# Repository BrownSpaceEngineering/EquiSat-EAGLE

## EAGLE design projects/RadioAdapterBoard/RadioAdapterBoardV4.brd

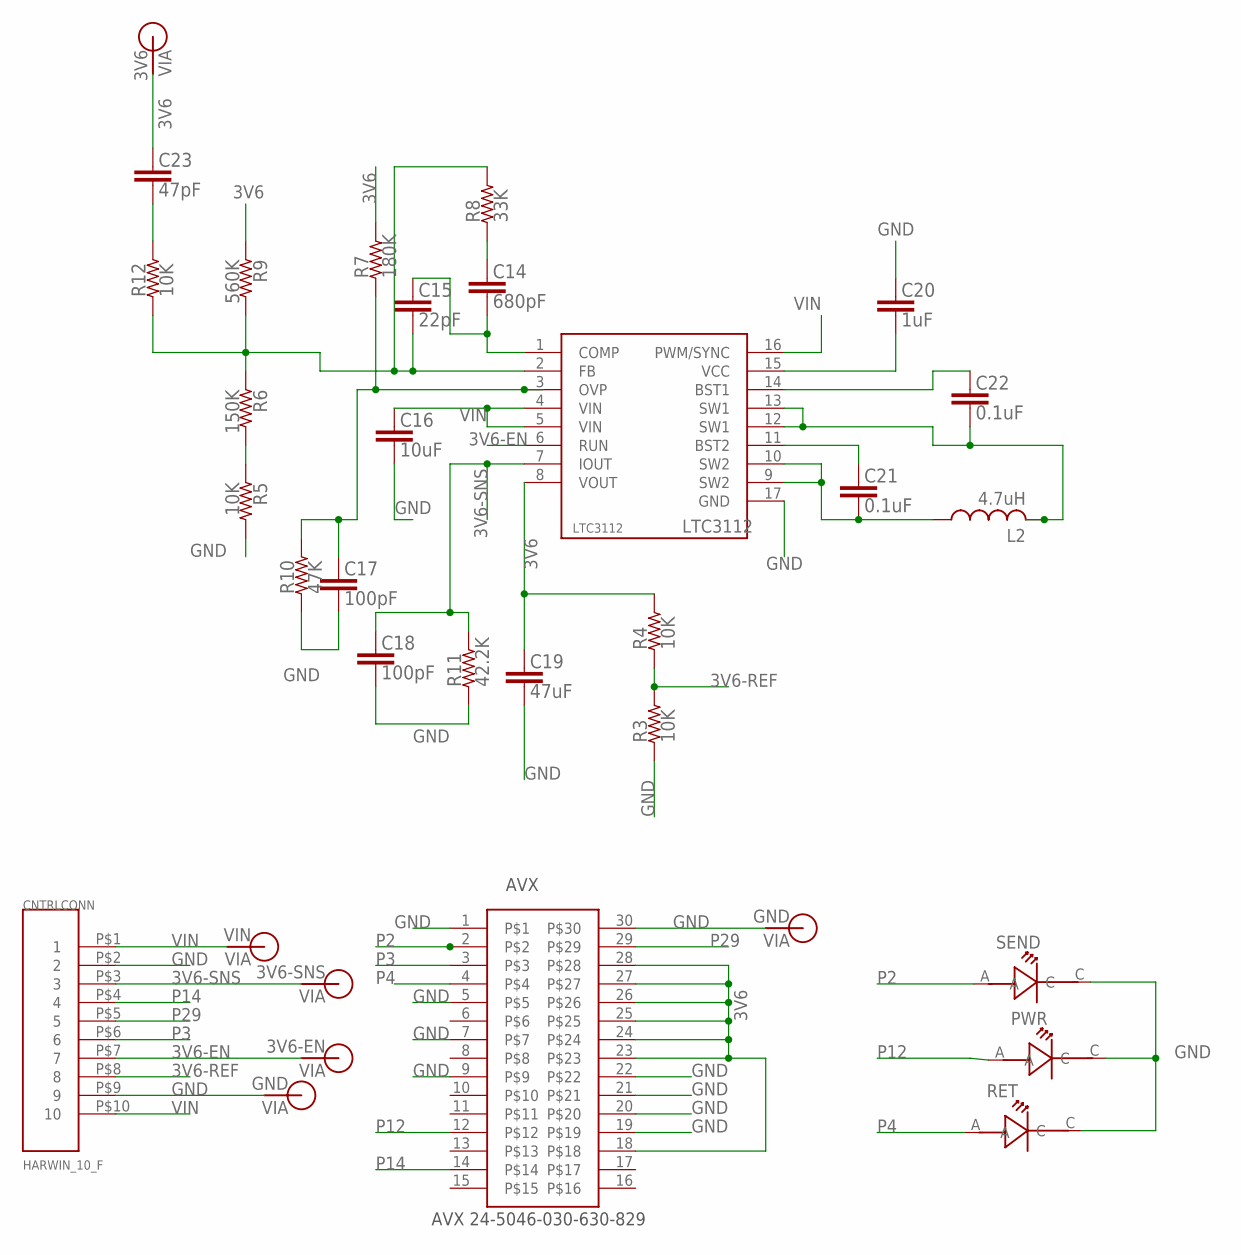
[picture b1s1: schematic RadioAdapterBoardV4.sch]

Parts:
AVX: AVX-24-5046-030-630-829; AVX-24-5046-630-829
C14: 680pF; 0805
C15: 22pF; 0805
C16: 10uF; 0805
C17, C18: 100pF; 0805
C19: 47uF; 0805
C20: 1uF; 0805
C21, C22: 0.1uF; 0805
C23: 47pF; 0805
CNTRLCONN: HARWIN_10_F; HARWIN_DATAMATE_10_F
L2: 4.7uH; L3225M
LTC3112: LTC3112; DHD16
PWR: LT-T673-Q1R2-25-Z; PLCC-2
R3, R4, R5, R12: 10K; 0805
R6: 150K; 0805
R7: 180K; 0805
R8: 33K; 0805
R9: 560K; 0805
R10: 47K; 0805
R11: 42.2K; 0805
RET: LT-T673-Q1R2-25-Z; PLCC-2
SEND: LT-T673-Q1R2-25-Z; PLCC-2
V1: VIN; VIA-60MIL-SQ
V2: 3V6-SNS; VIA-60MIL-SQ
V3, V4: GND; VIA-60MIL-SQ
V5: 3V6; VIA-60MIL-SQ
V6: 3V6-EN; VIA-60MIL-SQ

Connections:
3V6: AVX.18, AVX.23, AVX.24, AVX.25, AVX.26, AVX.27, AVX.28, C19.1, C23.1, LTC3112.8 (VOUT), R4.2, R7.2, R9.1, V5.P$1
3V6-EN: CNTRLCONN.P$7 (7), LTC3112.6 (RUN), V6.P$1
3V6-REF: CNTRLCONN.P$8 (8), R3.2, R4.1
3V6-SNS: C18.1, CNTRLCONN.P$3 (3), LTC3112.7 (IOUT), R11.2, V2.P$1
COMP: C14.2, C15.1, LTC3112.1 (COMP)
FB: C15.2, LTC3112.2 (FB), R6.1, R8.2, R9.2, R12.1
GND: AVX.1, AVX.5, AVX.7, AVX.9, AVX.19, AVX.20, AVX.21, AVX.22, AVX.30, C16.2, C17.2, C18.2, C19.2, C20.1, CNTRLCONN.P$2 (2), CNTRLCONN.P$9 (9), LTC3112.17 (GND), PWR.C, R3.1, R5.2, R10.1, R11.1, RET.C, SEND.C, V3.P$1, V4.P$1
unnamed: C14.1, R8.1
unnamed: C23.2, R12.2
unnamed: R5.1, R6.2
unnamed: C20.2, LTC3112.15 (VCC)
unnamed: C22.1, LTC3112.14 (BST1)
unnamed: C22.2, L2.2, LTC3112.12 (SW1), LTC3112.13 (SW1)
unnamed: C21.2, L2.1, LTC3112.9 (SW2), LTC3112.10 (SW2)
unnamed: C21.1, LTC3112.11 (BST2)
OVP: C17.1, LTC3112.3 (OVP), R7.1, R10.2
P2: AVX.2, SEND.A
P3: AVX.3, CNTRLCONN.P$6 (6)
P4: AVX.4, RET.A
P12: AVX.12, PWR.A
P14: AVX.14, CNTRLCONN.P$4 (4)
P29: AVX.29, CNTRLCONN.P$5 (5)
VIN: C16.1, CNTRLCONN.P$1 (1), CNTRLCONN.P$10 (10), LTC3112.4 (VIN), LTC3112.5 (VIN), LTC3112.16 (PWM/SYNC), V1.P$1

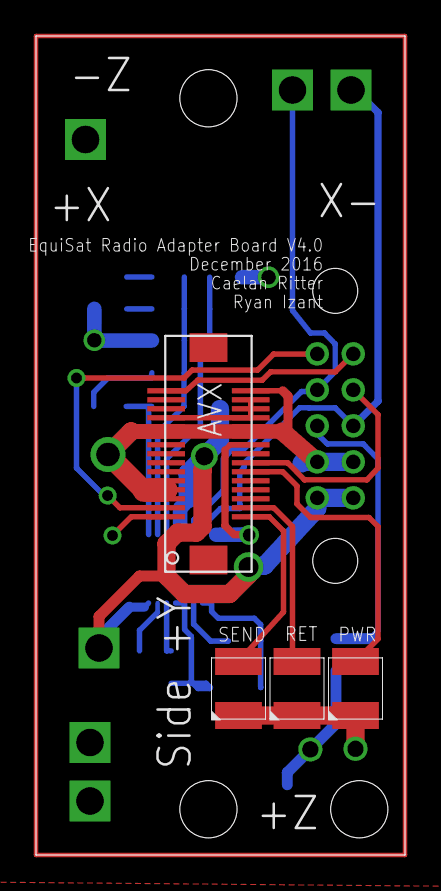
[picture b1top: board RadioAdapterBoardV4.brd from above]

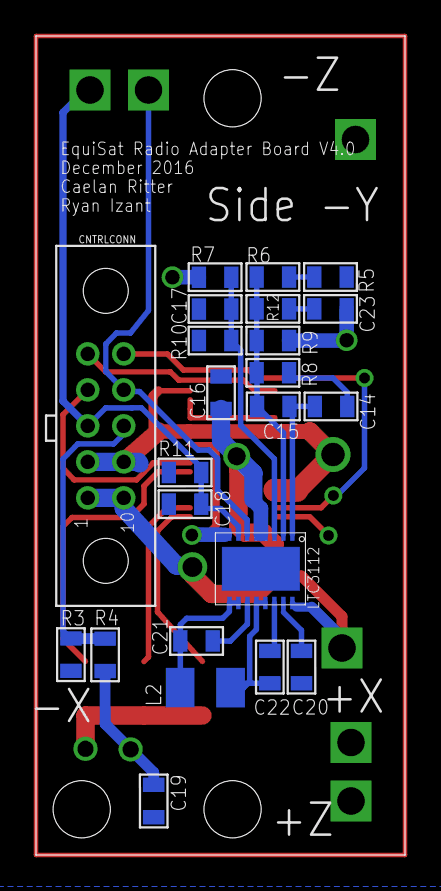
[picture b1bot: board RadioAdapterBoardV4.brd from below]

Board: 2 copper layers, 20.5 x 45.5 mm, 33 parts (23 on the bottom side), 23 nets.

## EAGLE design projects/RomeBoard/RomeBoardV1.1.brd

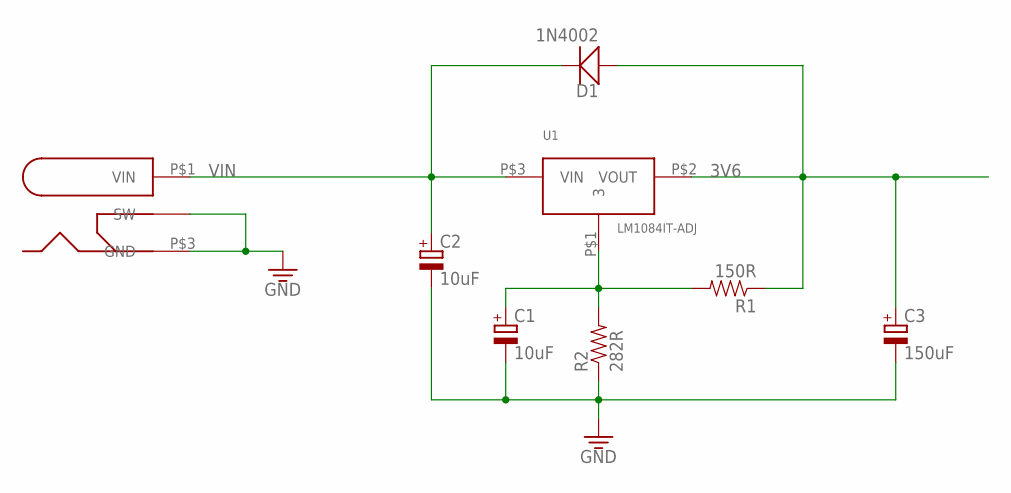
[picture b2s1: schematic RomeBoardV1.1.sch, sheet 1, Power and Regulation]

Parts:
C1, C2: 10uF; E2,5-7
C3: 150uF; E5-13
D1: 1N4002; DO-201AD
R1: 150R; AXIAL-0.4
R2: 282R; AXIAL-0.4
U1: LM1084IT-ADJ; TO-220-507302B00000G
U$2: PJ-002A

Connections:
3V6: C3.+, D1.P$1 (A), R1.1, U1.P$2 (VOUT); also elsewhere on the board
GND: C1.-, C2.-, C3.-, R2.1, U$2.P$2 (SW), U$2.P$3 (GND); also elsewhere on the board
unnamed: C1.+, R1.2, R2.2, U1.P$1 (3)
VIN: C2.+, D1.P$2 (C), U1.P$3 (VIN), U$2.P$1 (VIN); also elsewhere on the board

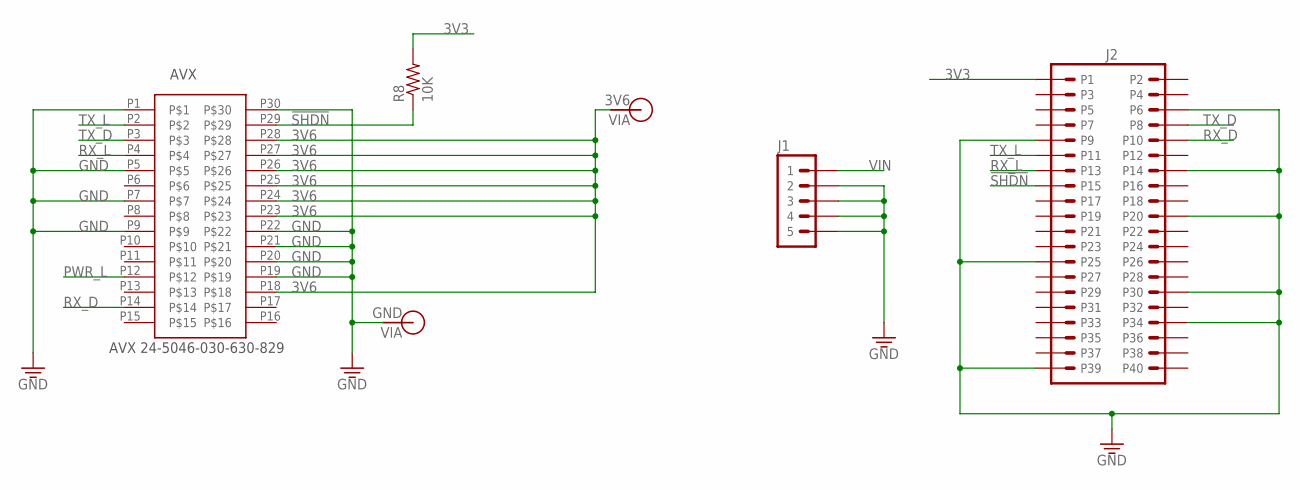
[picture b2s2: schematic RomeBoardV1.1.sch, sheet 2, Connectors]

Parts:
AVX: AVX-24-5046-030-630-829; AVX-24-5046-630-829
J1: HEADER-5; HEADER-05
J2: RASPBERRY-PI-HEADER; HEADER-20X02
R8: 10K; AXIAL-0.4
V4: GND; VIA-120MIL
V5: 3V6; VIA-120MIL

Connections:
3V3: J2.P1, R8.2
3V6: AVX.P18, AVX.P23, AVX.P24, AVX.P25, AVX.P26, AVX.P27, AVX.P28, V5.P$1; also elsewhere on the board
!SHDN: AVX.P29, J2.P15, R8.1
GND: AVX.P1, AVX.P5, AVX.P7, AVX.P9, AVX.P19, AVX.P20, AVX.P21, AVX.P22, AVX.P30, J1.2, J1.3, J1.4, J1.5, J2.P6, J2.P9, J2.P14, J2.P20, J2.P25, J2.P30, J2.P34, J2.P39, V4.P$1; also elsewhere on the board
PWR_L: AVX.P12; also elsewhere on the board
RX_D: AVX.P14, J2.P10; also elsewhere on the board
RX_L: AVX.P4, J2.P13; also elsewhere on the board
TX_D: AVX.P3, J2.P8; also elsewhere on the board
TX_L: AVX.P2, J2.P11; also elsewhere on the board
VIN: J1.1; also elsewhere on the board

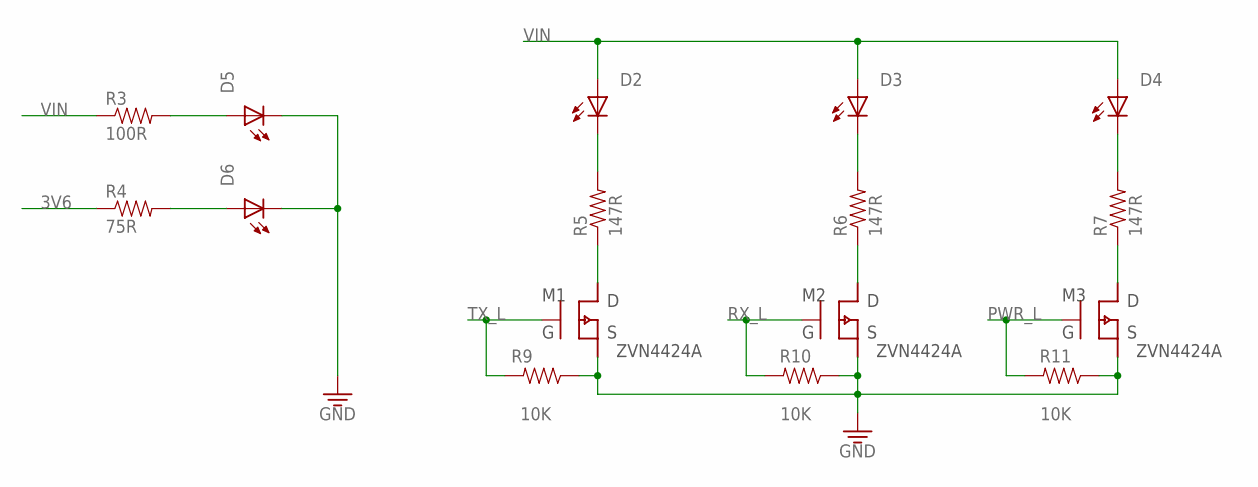
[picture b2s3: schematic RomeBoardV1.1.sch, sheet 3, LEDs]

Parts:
D2, D3, D4, D5, D6: LEDTHRU-HOLE-CONNECTOR; 1X2-POL
M1, M2, M3: ZVN4424A; TO-923-MOS
R3: 100R; AXIAL-0.4
R4: 75R; AXIAL-0.4
R5, R6, R7: 147R; AXIAL-0.4
R9, R10, R11: 10K; AXIAL-0.4

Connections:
3V6: R4.1; also elsewhere on the board
GND: D5.2 (C), D6.2 (C), M1.3 (S), M2.3 (S), M3.3 (S), R9.1, R10.1, R11.1; also elsewhere on the board
unnamed: D5.1 (A), R3.2
unnamed: D6.1 (A), R4.2
unnamed: D3.2 (C), R6.2
unnamed: M1.1 (D), R5.1
unnamed: M2.1 (D), R6.1
unnamed: M3.1 (D), R7.1
unnamed: D4.2 (C), R7.2
unnamed: D2.2 (C), R5.2
PWR_L: M3.2 (G), R11.2; also elsewhere on the board
RX_L: M2.2 (G), R10.2; also elsewhere on the board
TX_L: M1.2 (G), R9.2; also elsewhere on the board
VIN: D2.1 (A), D3.1 (A), D4.1 (A), R3.1; also elsewhere on the board

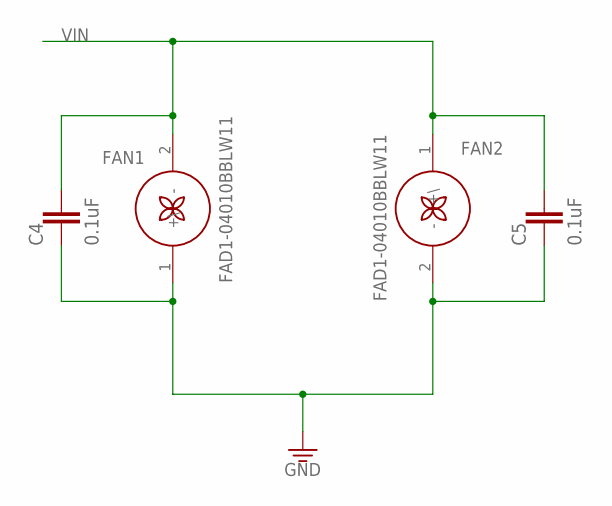
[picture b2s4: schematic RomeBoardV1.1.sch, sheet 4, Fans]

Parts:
C4, C5: 0.1uF; C050-025X075
FAN1, FAN2: FAD1-04010BBLW11; 1X2-POL

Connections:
GND: C4.2, C5.2, FAN1.1 (+\), FAN2.2 (-); also elsewhere on the board
VIN: C4.1, C5.1, FAN1.2 (-), FAN2.1 (+\); also elsewhere on the board

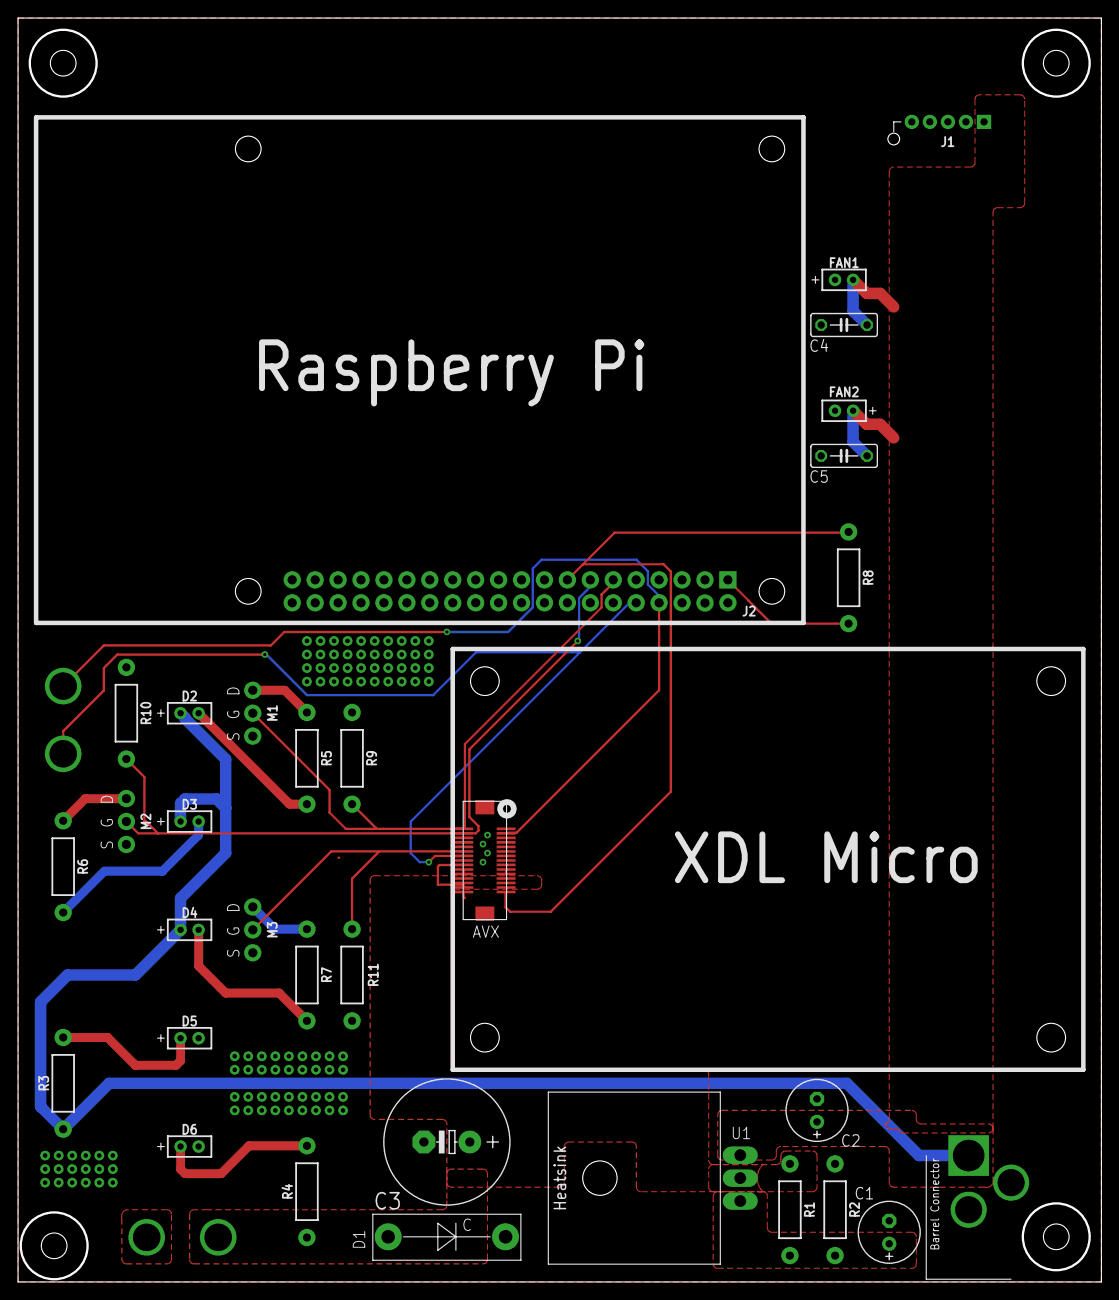
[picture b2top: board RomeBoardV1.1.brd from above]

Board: 2 copper layers, 120.0 x 140.0 mm, 36 parts (0 on the bottom side), 19 nets.

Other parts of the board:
V1: TX_D; VIA-120MIL
V2: RX_D; VIA-120MIL

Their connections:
RX_D: V2.P$1; also elsewhere on the board
TX_D: V1.P$1; also elsewhere on the board

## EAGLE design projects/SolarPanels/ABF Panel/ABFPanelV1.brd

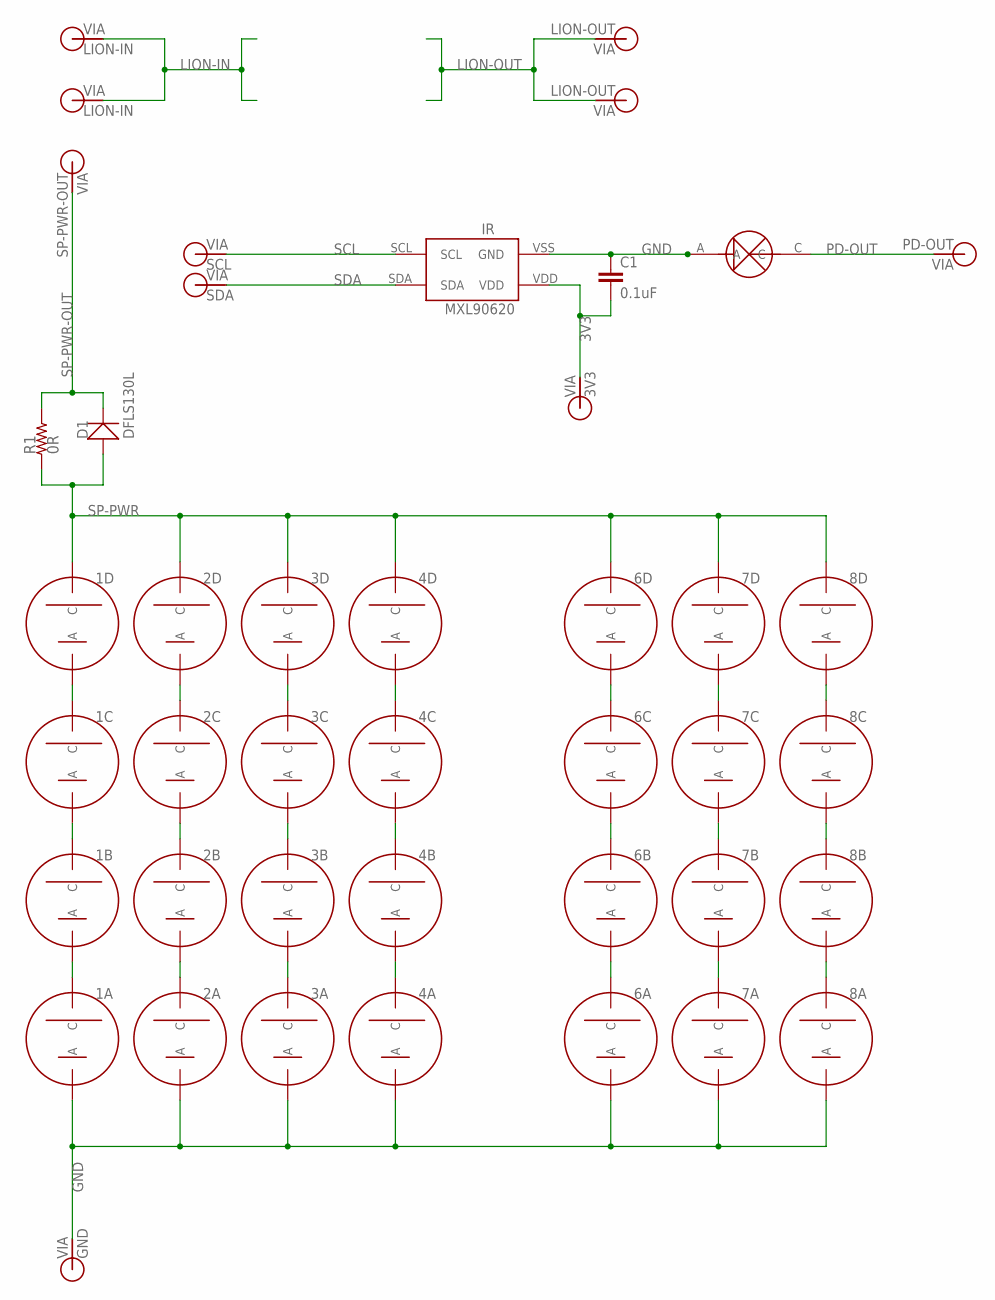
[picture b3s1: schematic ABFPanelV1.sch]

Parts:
1A, 1B, 1C, 1D, 2A, 2B, 2C, 2D, 3A, 3B, 3C, 3D, 4A, 4B, 4C, 4D, 6A, 6B, 6C, 6D, 7A, 7B, 7C, 7D, 8A, 8B, 8C, 8D: SOLARCELLV3; TRISOLX-V3
3V3: 3V3; VIA-60MIL
C1: 0.1uF; 0805
D1: DFLS130L; PWRDI-123
GND: GND; VIA-60MIL
IR: MXL90620
PD: PHOTODETECTOR; PHOTODECTORDEVICE2
PD-OUT: PD-OUT; VIA-60MIL
PWR-OUT: SP-PWR-OUT; VIA-60MIL
R1: 0R; 1210
SCL: SCL; VIA-60MIL
SDA: SDA; VIA-60MIL
V1, V2: LION-IN; VIA-60MIL
V3, V4: LION-OUT; VIA-60MIL

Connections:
3V3: 3V3.P$1, C1.2, IR.VDD
GND: 1A.ANODE (A), 2A.ANODE (A), 3A.ANODE (A), 4A.ANODE (A), 6A.ANODE (A), 7A.ANODE (A), 8A.ANODE (A), C1.1, GND.P$1, IR.VSS (GND), PD.A
LION-IN: V1.P$1, V2.P$1
LION-OUT: V3.P$1, V4.P$1
unnamed: 2C.CATHODE (C), 2D.ANODE (A)
unnamed: 1C.CATHODE (C), 1D.ANODE (A)
unnamed: 1B.CATHODE (C), 1C.ANODE (A)
unnamed: 1A.CATHODE (C), 1B.ANODE (A)
unnamed: 2B.CATHODE (C), 2C.ANODE (A)
unnamed: 2A.CATHODE (C), 2B.ANODE (A)
unnamed: 3C.CATHODE (C), 3D.ANODE (A)
unnamed: 3B.CATHODE (C), 3C.ANODE (A)
unnamed: 3A.CATHODE (C), 3B.ANODE (A)
unnamed: 4C.CATHODE (C), 4D.ANODE (A)
unnamed: 4B.CATHODE (C), 4C.ANODE (A)
unnamed: 4A.CATHODE (C), 4B.ANODE (A)
unnamed: 6C.CATHODE (C), 6D.ANODE (A)
unnamed: 6B.CATHODE (C), 6C.ANODE (A)
unnamed: 6A.CATHODE (C), 6B.ANODE (A)
unnamed: 7C.CATHODE (C), 7D.ANODE (A)
unnamed: 7B.CATHODE (C), 7C.ANODE (A)
unnamed: 7A.CATHODE (C), 7B.ANODE (A)
unnamed: 8C.CATHODE (C), 8D.ANODE (A)
unnamed: 8B.CATHODE (C), 8C.ANODE (A)
unnamed: 8A.CATHODE (C), 8B.ANODE (A)
PD-OUT: PD.C, PD-OUT.P$1
SCL: IR.SCL, SCL.P$1
SDA: IR.SDA, SDA.P$1
SP-PWR: 1D.CATHODE (C), 2D.CATHODE (C), 3D.CATHODE (C), 4D.CATHODE (C), 6D.CATHODE (C), 7D.CATHODE (C), 8D.CATHODE (C), D1.A, R1.P$1 (1)
SP-PWR-OUT: D1.C, PWR-OUT.P$1, R1.P$2 (2)

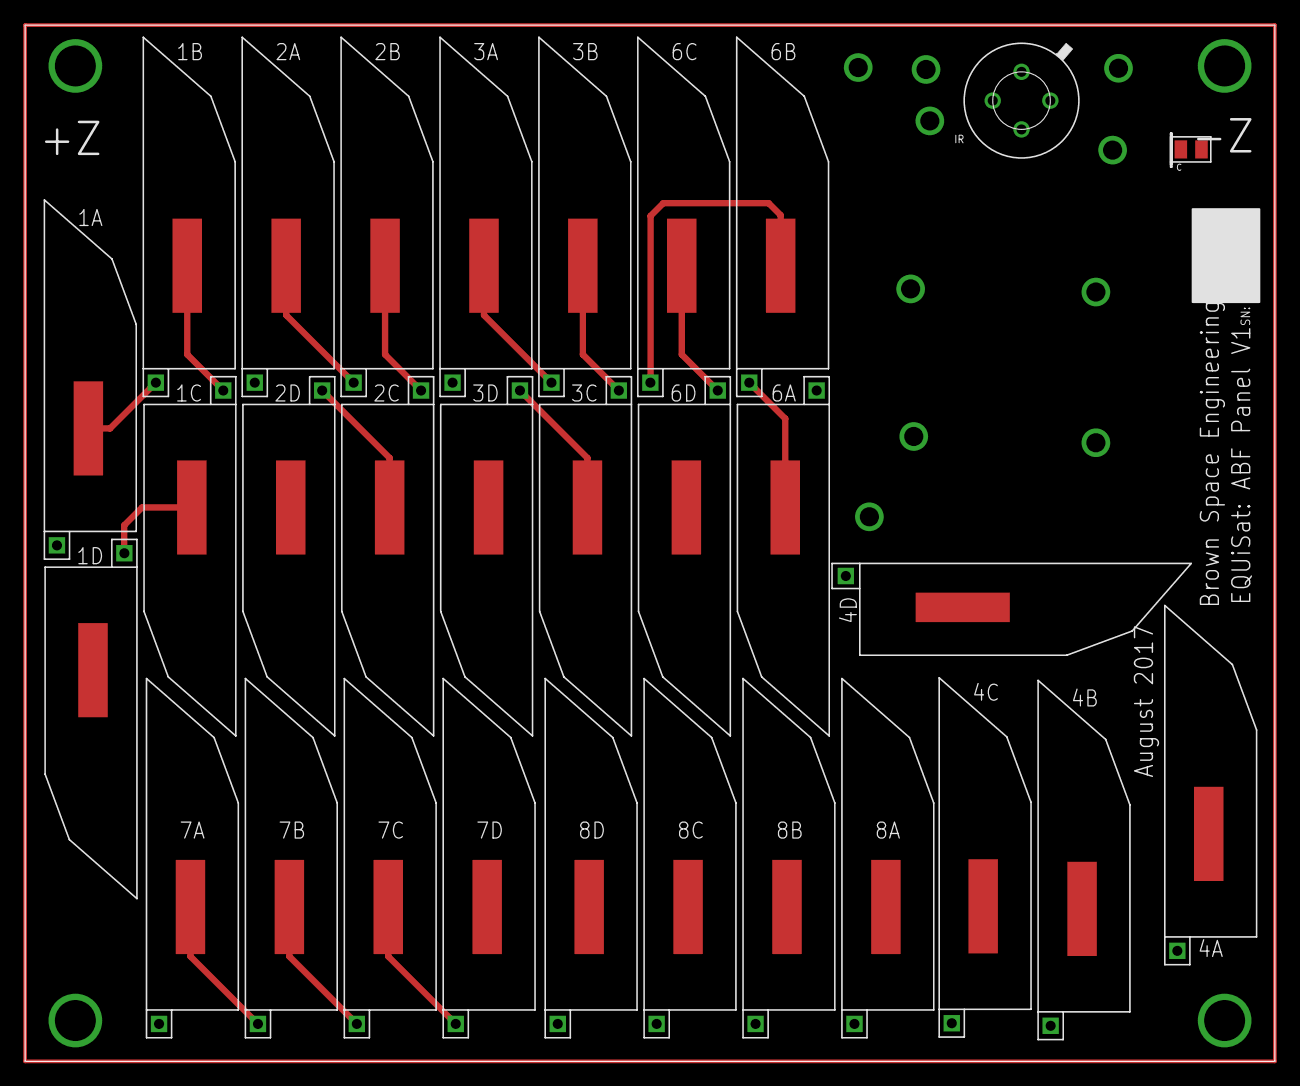
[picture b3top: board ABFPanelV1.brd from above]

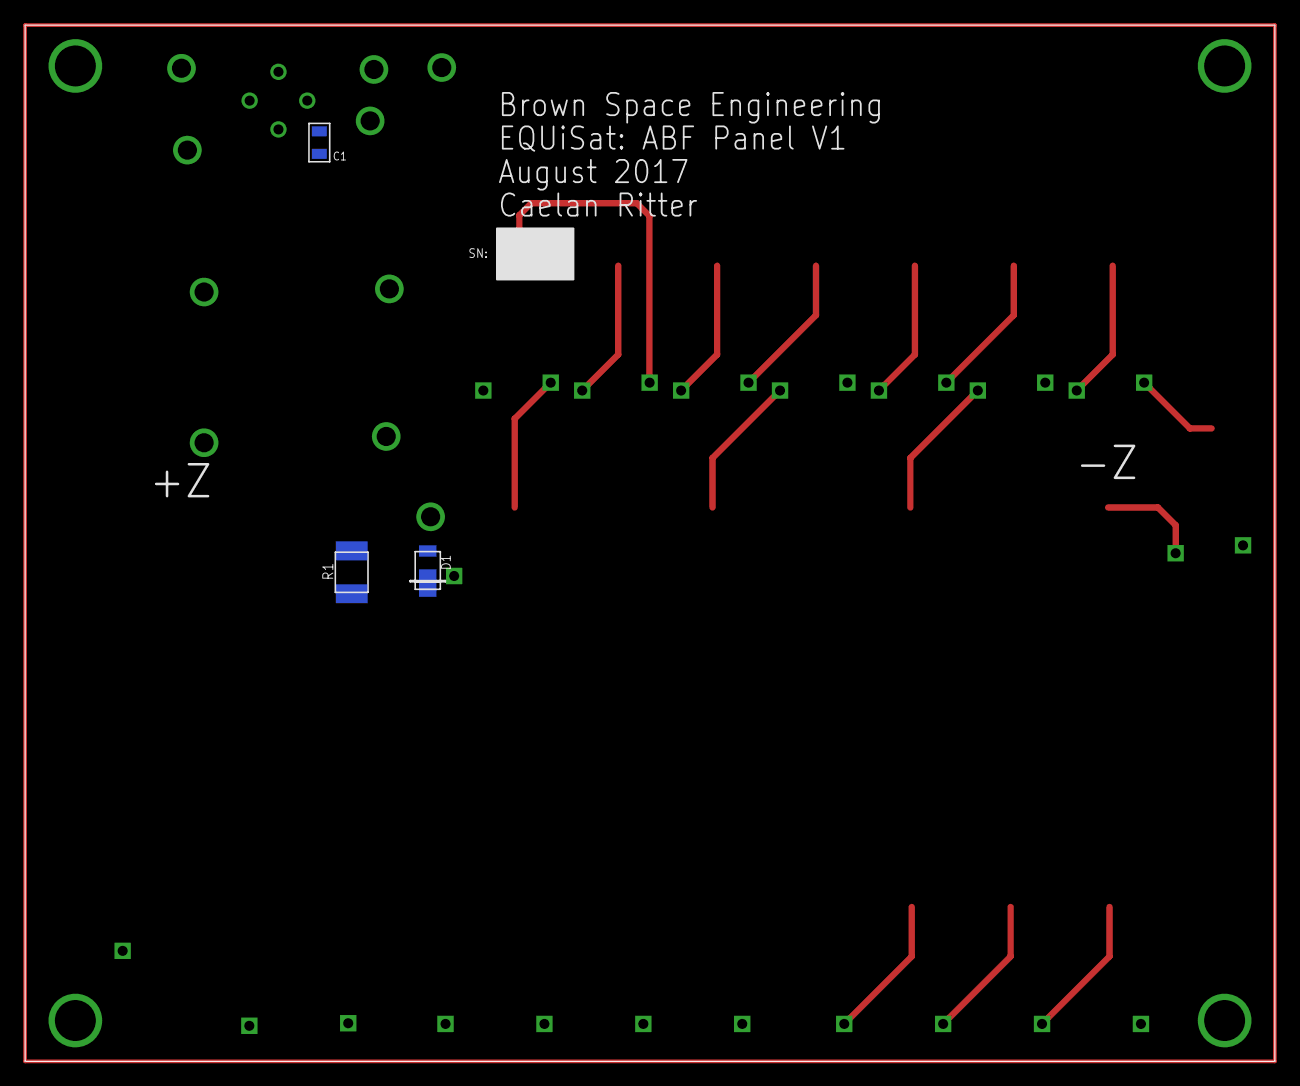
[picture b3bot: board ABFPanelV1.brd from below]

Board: 2 copper layers, 99.5 x 82.5 mm, 43 parts (3 on the bottom side), 30 nets.
